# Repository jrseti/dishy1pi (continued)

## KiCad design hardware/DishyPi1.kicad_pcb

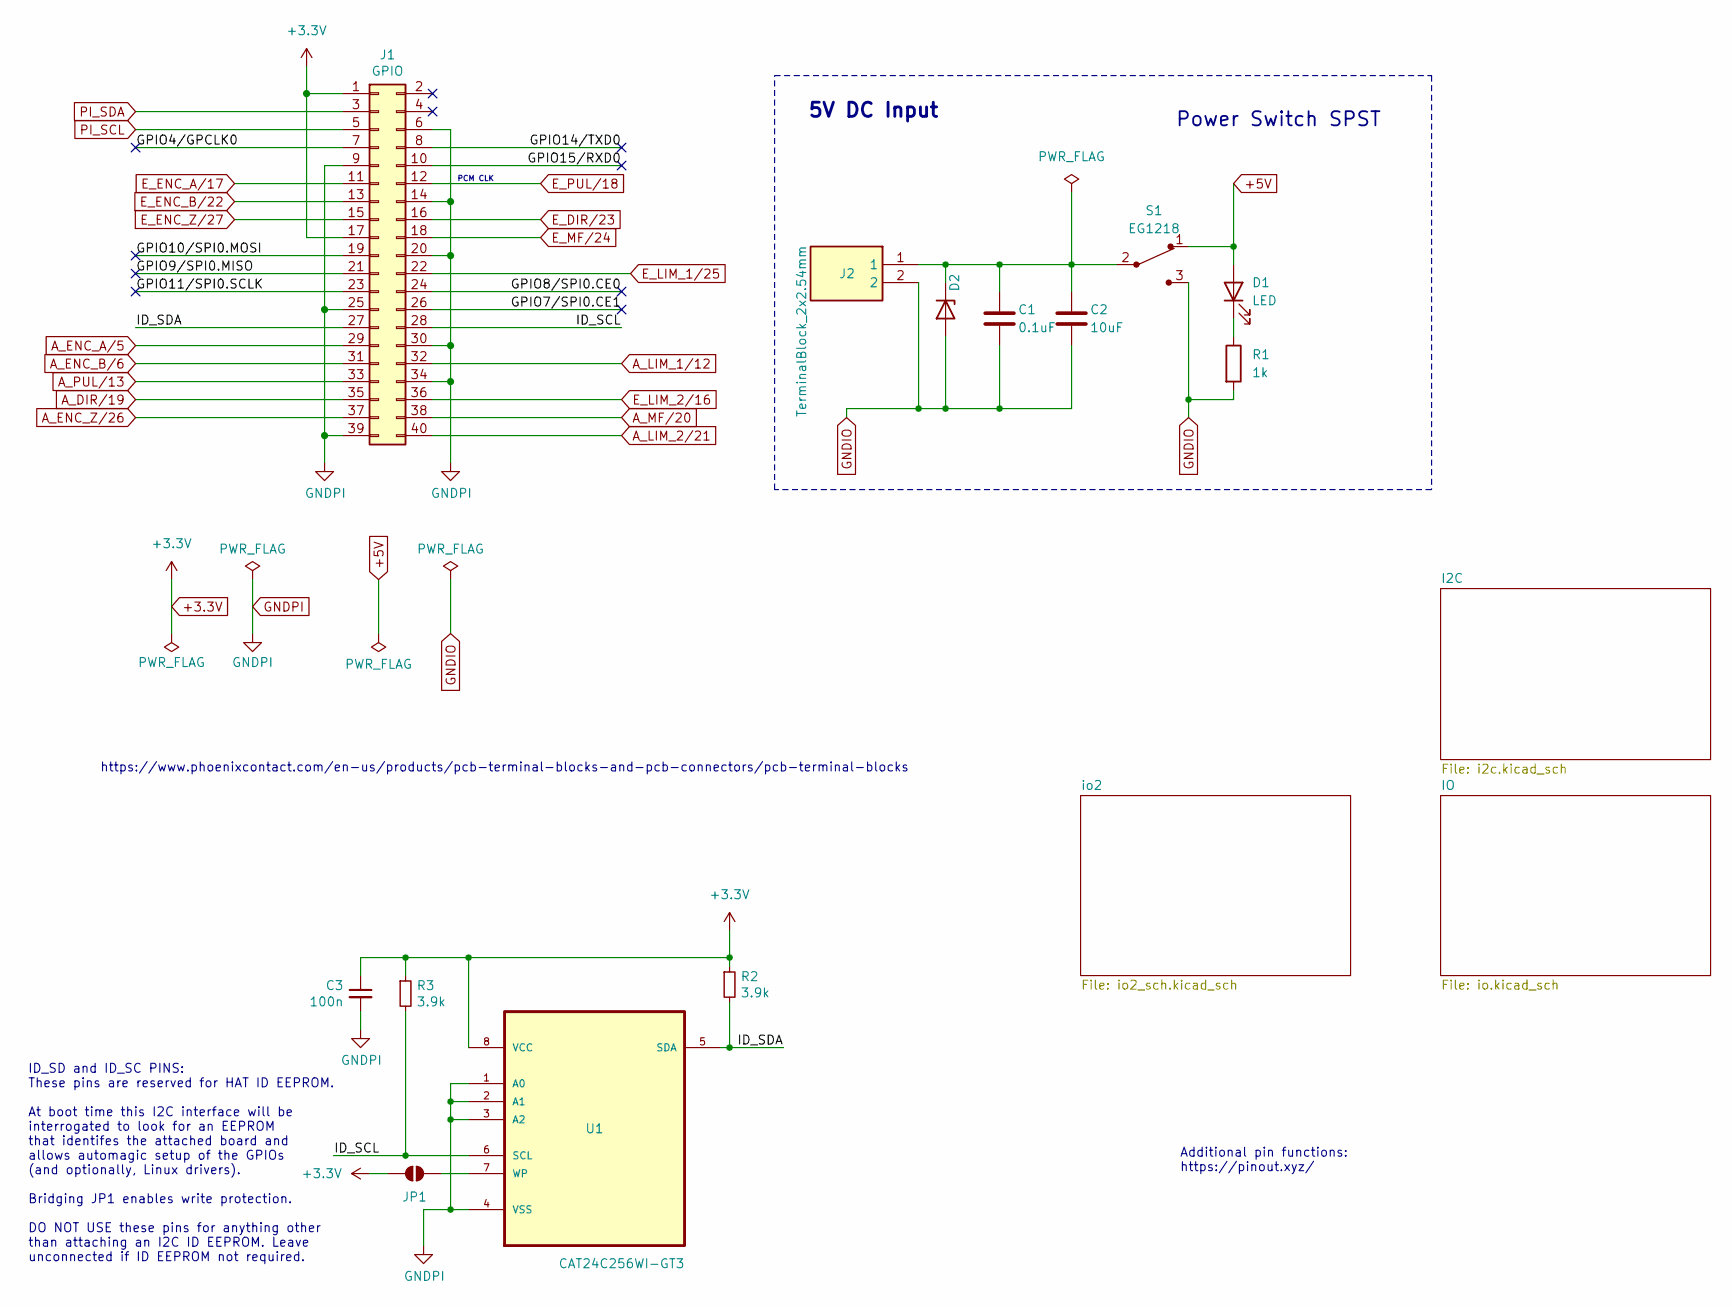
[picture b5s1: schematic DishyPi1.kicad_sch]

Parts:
C1: 0.1uF; C_0402_1005Metric
C2: 10uF; C_0402_1005Metric
C3: 100n; C_0402_1005Metric
D1: LED; LED_1206_3216Metric; LCSC Part C5264252
D2: TPESD0402G05V; D_0402_1005Metric; LCSC C558615
J1: GPIO; PinSocket_2x20_P2.54mm_Vertical
J2: TerminalBlock_2x2.54mm; Manufacturer_Part_Number 1725656; Mouser Part Number 651-1725656
JP1: JP1; Header 1x2 Male
R1: 1k; R_0402_1005Metric; LCSC Part C4410
R2, R3: 3.9k; R_0402_1005Metric
S1: EG1218; Switch_Slide_11.6x4mm_EG1218; MPN EG1218; Digi-Key_PN EG1903-ND
U1: CAT24C256WI-GT3; CAT24C256_EEPROM; MPN CAT24C256WI-GT3

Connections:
+3.3V: C3.1, J1.1, J1.17, JP1.1 (A), R2.1, R3.1, U1.8 (VCC); also elsewhere on the board
+5V: D1.2 (A), S1.1; also elsewhere on the board
/GPIO4/GPCLK0: J1.7
/GPIO7/SPI0.CE1: J1.26
/GPIO8/SPI0.CE0: J1.24
/GPIO9/SPI0.MISO: J1.21
/GPIO10/SPI0.MOSI: J1.19
/GPIO11/SPI0.SCLK: J1.23
/GPIO14/TXD0: J1.8
/GPIO15/RXD0: J1.10
/ID_SCL: J1.28, R3.2, U1.6 (SCL)
/ID_SDA: J1.27, R2.2, U1.5 (SDA)
A_DIR/19: J1.35; also elsewhere on the board
A_ENC_A/5: J1.29; also elsewhere on the board
A_ENC_B/6: J1.31; also elsewhere on the board
A_ENC_Z/26: J1.37; also elsewhere on the board
A_LIM_1/12: J1.32; also elsewhere on the board
A_LIM_2/21: J1.40; also elsewhere on the board
A_MF/20: J1.38; also elsewhere on the board
A_PUL/13: J1.33; also elsewhere on the board
E_DIR/23: J1.16; also elsewhere on the board
E_ENC_A/17: J1.11; also elsewhere on the board
E_ENC_B/22: J1.13; also elsewhere on the board
E_ENC_Z/27: J1.15; also elsewhere on the board
E_LIM_1/25: J1.22; also elsewhere on the board
E_LIM_2/16: J1.36; also elsewhere on the board
E_MF/24: J1.18; also elsewhere on the board
E_PUL/18: J1.12; also elsewhere on the board
GNDIO: C1.2, C2.2, D2.2 (A), J2.2, R1.2, S1.3; also elsewhere on the board
GNDPI: C3.2, J1.6, J1.9, J1.14, J1.20, J1.25, J1.30, J1.34, J1.39, U1.1 (A0), U1.2 (A1), U1.3 (A2), U1.4 (VSS); also elsewhere on the board
unnamed: D1.1 (K), R1.1
unnamed: C1.1, C2.1, D2.1 (K), J2.1, S1.2
unnamed: JP1.2 (B), U1.7 (WP)
PI_SCL: J1.5; also elsewhere on the board
PI_SDA: J1.3; also elsewhere on the board

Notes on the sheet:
PCM CLK
Additional pin functions: https://pinout.xyz/
Power Switch SPST
ID_SD and ID_SC PINS: These pins are reserved for HAT ID EEPROM. At boot time this I2C interface will be interrogated to look for an EEPROM that identifes the attached board and allows automagic setup of the GPIOs (and optionally, Linux drivers). Bridging JP1 enables write protection. DO NOT USE th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
https://www.phoenixcontact.com/en-us/products/pcb-terminal-blocks-and-pcb-connectors/pcb-terminal-blocks
5V DC Input

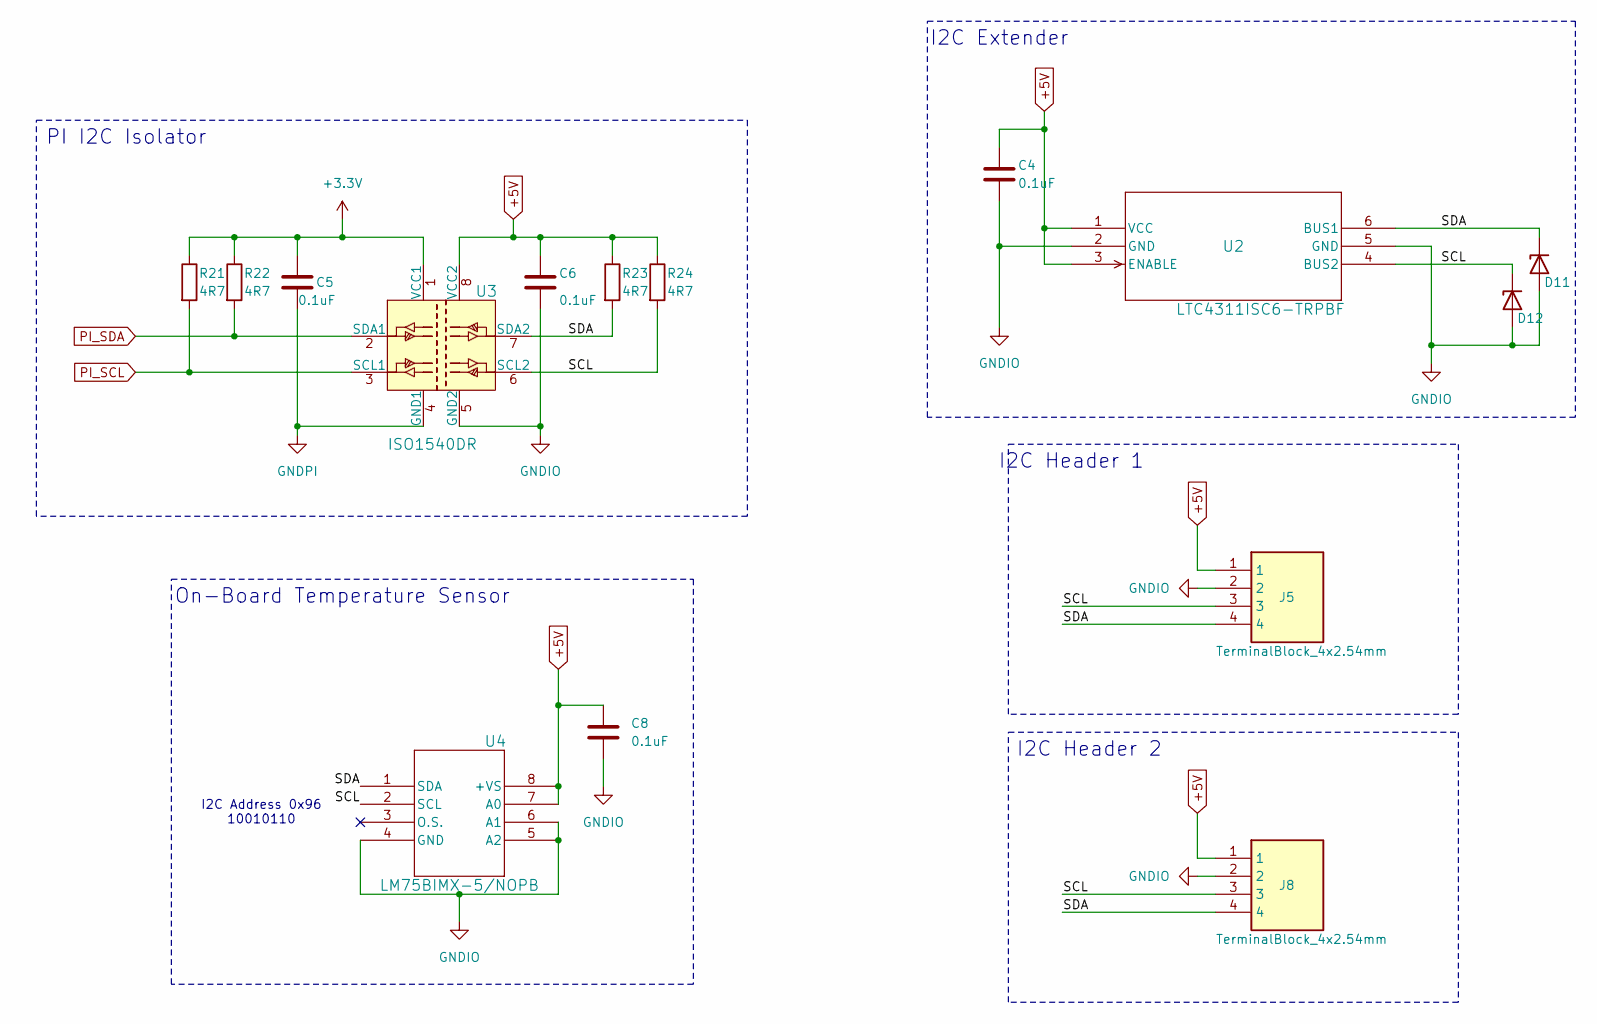
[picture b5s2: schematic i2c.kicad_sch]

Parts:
C4, C5, C6, C8: 0.1uF; C_0402_1005Metric
D11, D12: TPESD0402G05V; D_0402_1005Metric; LCSC C558615
J5, J8: TerminalBlock_4x2.54mm; Manufacturer_Part_Number 1725672; Mouser Part Number 651-1725672
R21, R22, R23, R24: 4R7; R_0402_1005Metric
U2: LTC4311ISC6-TRPBF; LTC4311
U3: ISO1540DR; SOIC-8_W3.9mm; MPN ISO1540DR; Digi-Key_PN 296-34871-1-ND
U4: LM75BIMX-5/NOPB; M08A

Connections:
+3.3V: C5.1, R21.1, R22.1, U3.1 (VCC1); also elsewhere on the board
+5V: C4.1, C6.1, C8.2, J5.1, J8.1, R23.1, R24.1, U2.1 (VCC), U2.3 (ENABLE), U3.8 (VCC2), U4.7 (A0), U4.8 (+VS); also elsewhere on the board
/I2C/SCL: D12.1 (K), J5.3, J8.3, R24.2, U2.4 (BUS2), U3.6 (SCL2), U4.2 (SCL)
/I2C/SDA: D11.1 (K), J5.4, J8.4, R23.2, U2.6 (BUS1), U3.7 (SDA2), U4.1 (SDA)
GNDIO: C4.2, C6.2, C8.1, D11.2 (A), D12.2 (A), J5.2, J8.2, U2.2 (GND), U2.5 (GND), U3.5 (GND2), U4.4 (GND), U4.5 (A2), U4.6 (A1); also elsewhere on the board
GNDPI: C5.2, U3.4 (GND1); also elsewhere on the board
PI_SCL: R21.2, U3.3 (SCL1); also elsewhere on the board
PI_SDA: R22.2, U3.2 (SDA1); also elsewhere on the board

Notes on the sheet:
I2C Header 1
I2C Header 2
PI I2C Isolator
I2C Extender
On-Board Temperature Sensor
I2C Address 0x96 10010110

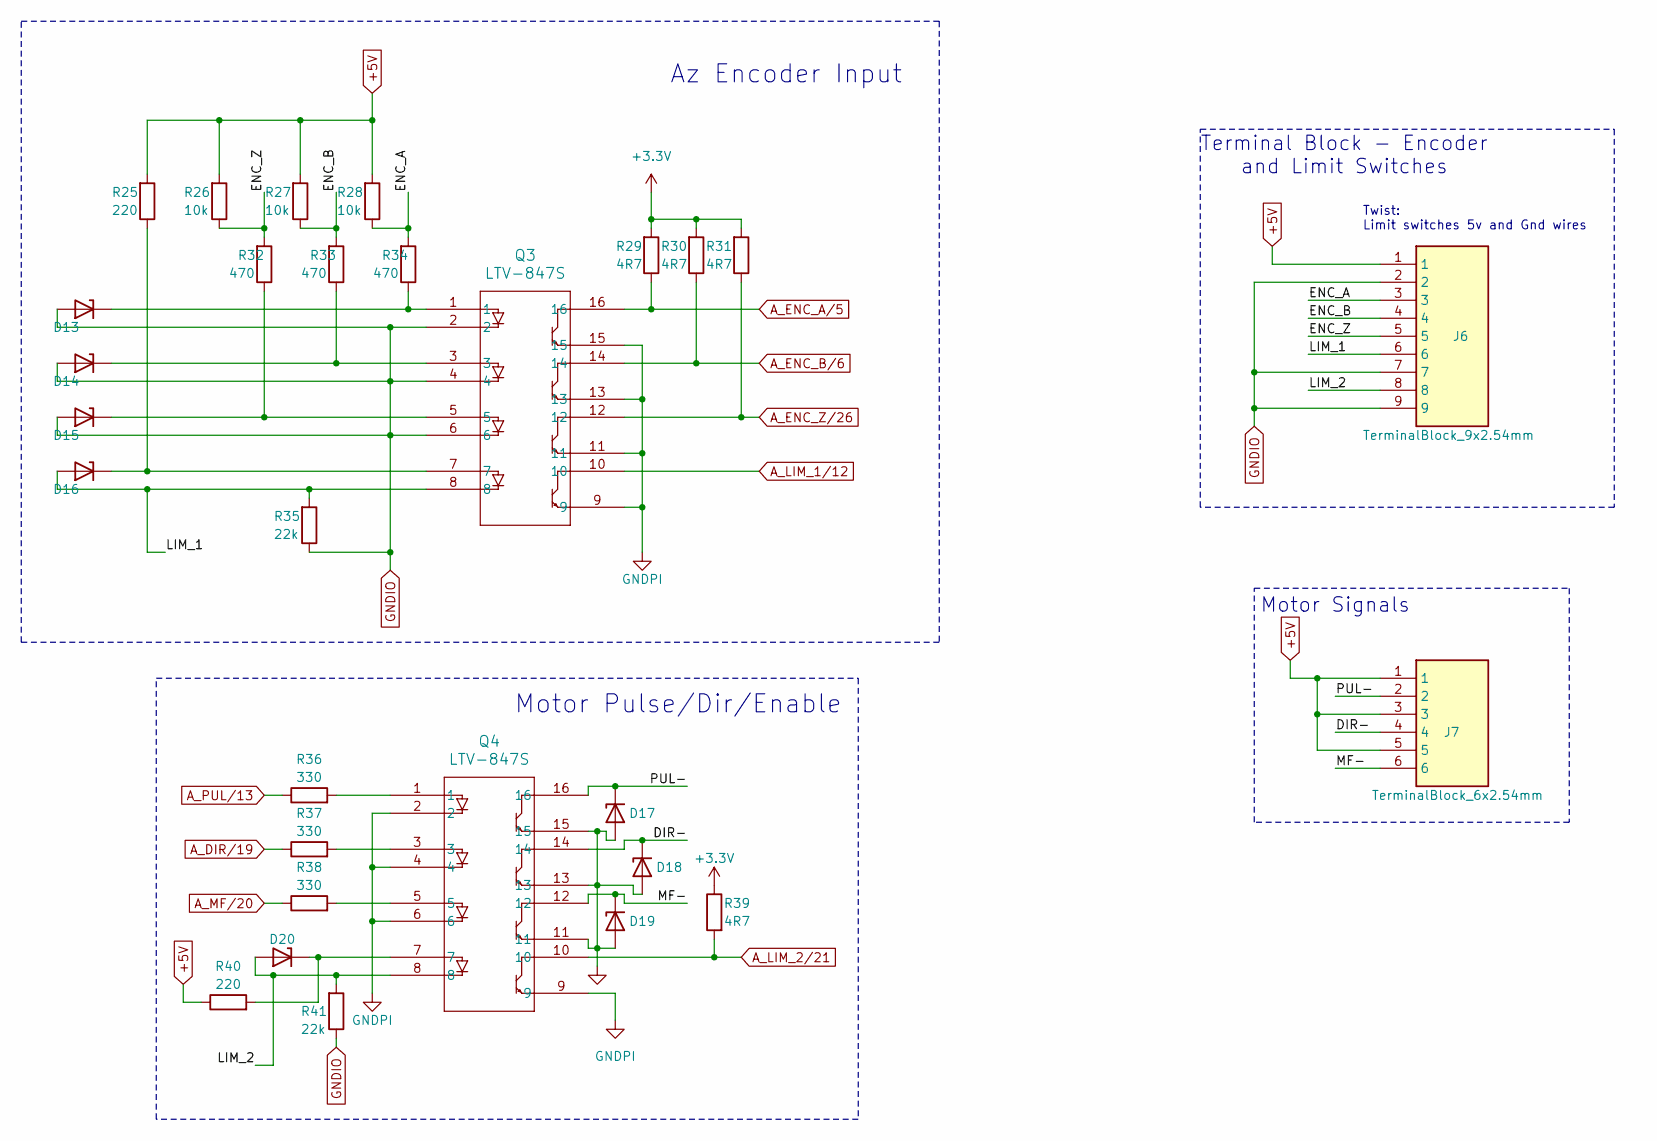
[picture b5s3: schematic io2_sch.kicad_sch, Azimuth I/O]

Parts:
D13, D14, D15, D16, D17, D18, D19, D20: TPESD0402G05V; D_0402_1005Metric; LCSC C558615
J6: TerminalBlock_9x2.54mm; Manufacturer_Part_Number 1725724; Mouser Part Number 651-1725724
J7: TerminalBlock_6x2.54mm; Manufacturer_Part_Number 1725698; Mouser Part Number 651-1725698
Q3, Q4: LTV-847S; ACPL-847-300E
R25, R40: 220; R_0402_1005Metric
R26, R27, R28: 10k; R_0402_1005Metric
R29, R30, R31, R39: 4R7; R_0402_1005Metric
R32, R33, R34: 470; R_0402_1005Metric
R35: 22k; R_0201_0603Metric
R36, R37, R38: 330; R_0402_1005Metric
R41: 22k; R_0402_1005Metric

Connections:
+3.3V: R29.2, R30.2, R31.2, R39.1; also elsewhere on the board
+5V: J6.1, J7.1, J7.3, J7.5, R25.2, R26.2, R27.2, R28.2, R40.1; also elsewhere on the board
/io2/DIR-: D18.1 (K), J7.4, Q4.14
/io2/ENC_A: J6.3, R28.1, R34.2
/io2/ENC_B: J6.4, R27.1, R33.2
/io2/ENC_Z: J6.5, R26.1, R32.2
/io2/LIM_1: D16.2 (A), J6.6, Q3.8, R35.2
/io2/LIM_2: D20.2 (A), J6.8, Q4.8, R41.2
/io2/MF-: D19.1 (K), J7.6, Q4.12
/io2/PUL-: D17.1 (K), J7.2, Q4.16
A_DIR/19: R37.1; also elsewhere on the board
A_ENC_A/5: Q3.16, R29.1; also elsewhere on the board
A_ENC_B/6: Q3.14, R30.1; also elsewhere on the board
A_ENC_Z/26: Q3.12, R31.1; also elsewhere on the board
A_LIM_1/12: Q3.10; also elsewhere on the board
A_LIM_2/21: Q4.10, R39.2; also elsewhere on the board
A_MF/20: R38.1; also elsewhere on the board
A_PUL/13: R36.1; also elsewhere on the board
GNDIO: D13.2 (A), D14.2 (A), D15.2 (A), D17.2 (A), D18.2 (A), D19.2 (A), J6.2, J6.7, J6.9, Q3.2, Q3.4, Q3.6, Q4.11, Q4.13, Q4.15, R35.1, R41.1; also elsewhere on the board
GNDPI: Q3.9, Q3.11, Q3.13, Q3.15, Q4.2, Q4.4, Q4.6, Q4.9; also elsewhere on the board
unnamed: D13.1 (K), Q3.1, R34.1
unnamed: D14.1 (K), Q3.3, R33.1
unnamed: D15.1 (K), Q3.5, R32.1
unnamed: D16.1 (K), Q3.7, R25.1
unnamed: D20.1 (K), Q4.7, R40.2
unnamed: Q4.1, R36.2
unnamed: Q4.3, R37.2
unnamed: Q4.5, R38.2

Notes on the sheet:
Az Encoder Input
Twist: Limit switches 5v and Gnd wires
Motor Signals
Terminal Block - Encoder and Limit Switches
Motor Pulse/Dir/Enable

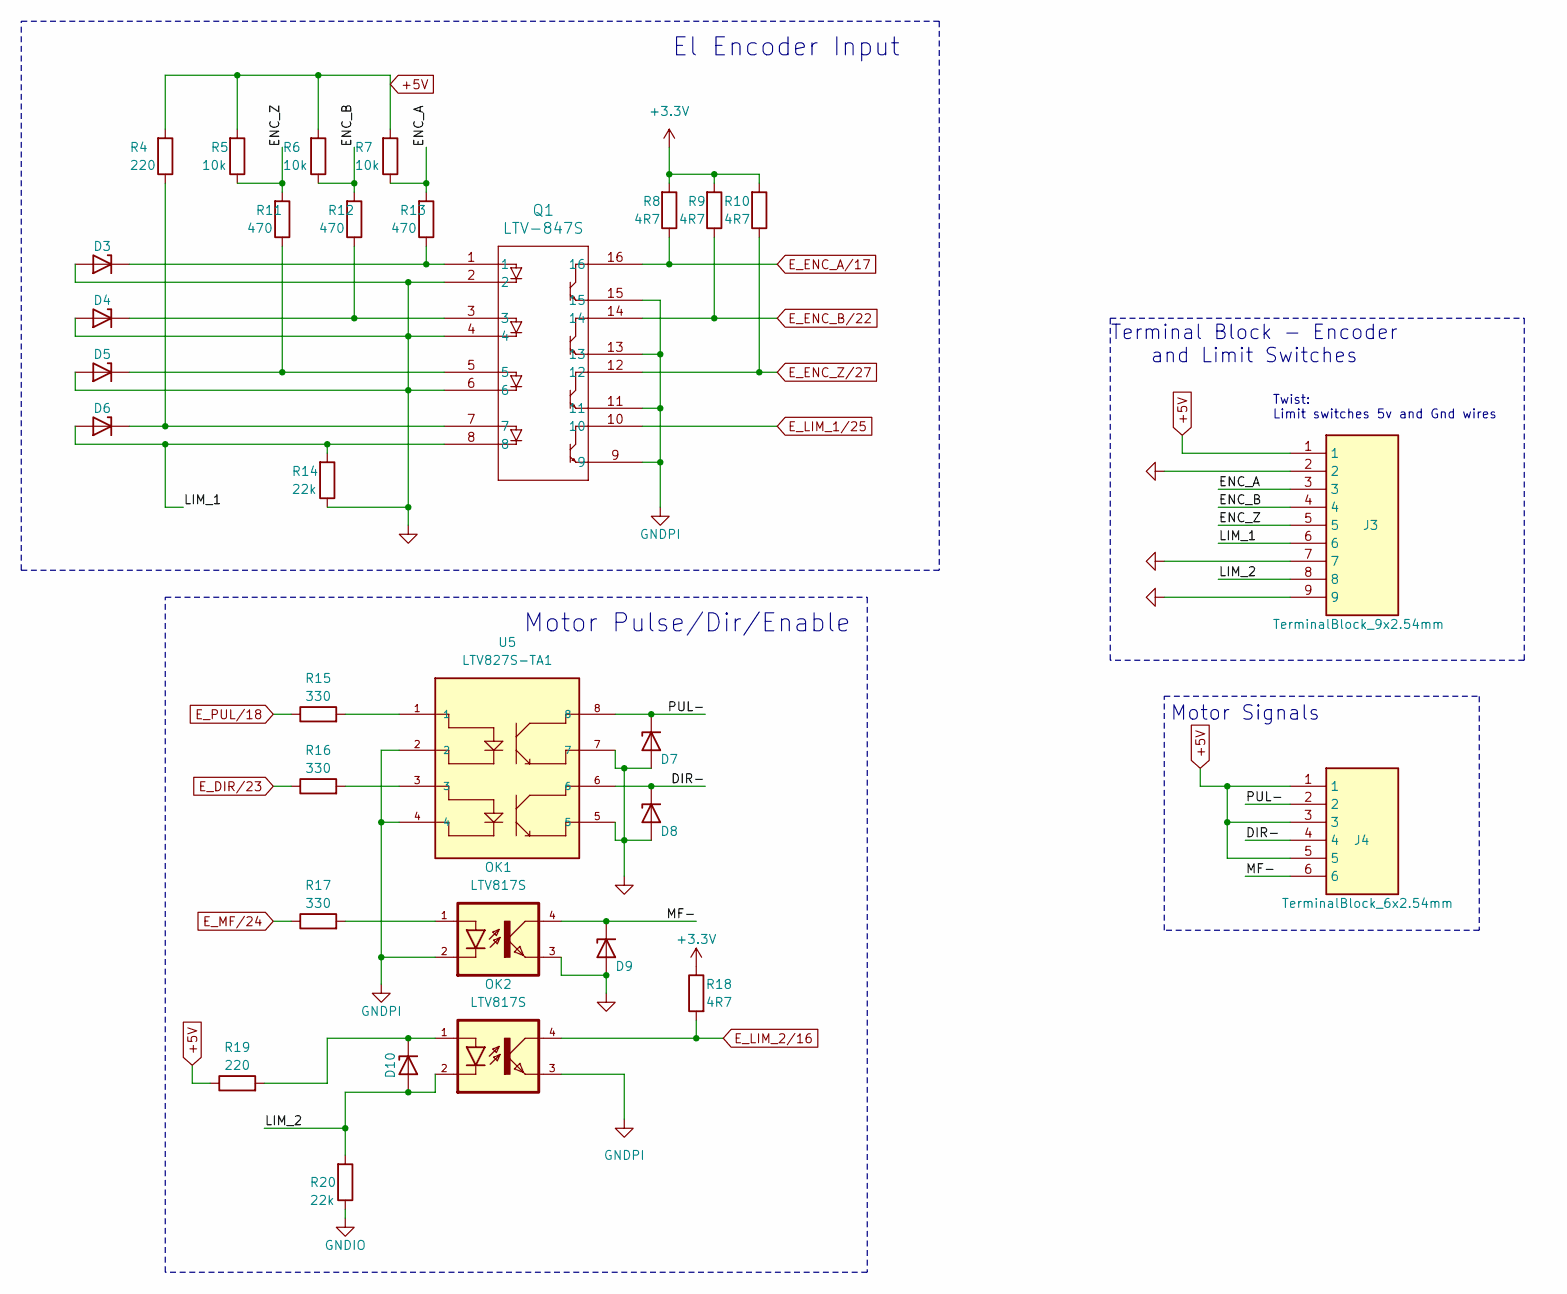
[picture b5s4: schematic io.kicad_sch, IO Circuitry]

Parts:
D3, D4, D5, D6, D7, D8, D9, D10: TPESD0402G05V; D_0402_1005Metric; LCSC C558615
J3: TerminalBlock_9x2.54mm; Manufacturer_Part_Number 1725724; Mouser Part Number 651-1725724
J4: TerminalBlock_6x2.54mm; Manufacturer_Part_Number 1725698; Mouser Part Number 651-1725698
OK1, OK2: LTV817S; MPN LTV-817S; LCSC C125121
Q1: LTV-847S; LTV847S
R4, R19: 220; R_0402_1005Metric
R5, R6, R7: 10k; R_0402_1005Metric
R8, R9, R10, R18: 4R7; R_0402_1005Metric
R11, R12, R13: 470; R_0402_1005Metric
R14, R20: 22k; R_0402_1005Metric
R15, R16, R17: 330; R_0402_1005Metric
U5: LTV827S-TA1; LTV827S; PARTNO 160-2040-1-ND; DigiKey_Part_Number 160-2040-1-ND

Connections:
+3.3V: R8.2, R9.2, R10.2, R18.1; also elsewhere on the board
+5V: J3.1, J4.1, J4.3, J4.5, R4.2, R5.2, R6.2, R7.2, R19.1; also elsewhere on the board
/IO/DIR-: D8.1 (K), J4.4, U5.6
/IO/ENC_A: J3.3, R7.1, R13.2
/IO/ENC_B: J3.4, R6.1, R12.2
/IO/ENC_Z: J3.5, R5.1, R11.2
/IO/LIM_1: D6.2 (A), J3.6, Q1.8, R14.2
/IO/LIM_2: D10.2 (A), J3.8, OK2.2, R20.2
/IO/MF-: D9.1 (K), J4.6, OK1.4
/IO/PUL-: D7.1 (K), J4.2, U5.8
E_DIR/23: R16.1; also elsewhere on the board
E_ENC_A/17: Q1.16, R8.1; also elsewhere on the board
E_ENC_B/22: Q1.14, R9.1; also elsewhere on the board
E_ENC_Z/27: Q1.12, R10.1; also elsewhere on the board
E_LIM_1/25: Q1.10; also elsewhere on the board
E_LIM_2/16: OK2.4, R18.2; also elsewhere on the board
E_MF/24: R17.1; also elsewhere on the board
E_PUL/18: R15.1; also elsewhere on the board
GNDIO: D3.2 (A), D4.2 (A), D5.2 (A), D7.2 (A), D8.2 (A), D9.2 (A), J3.2, J3.7, J3.9, OK1.3, Q1.2, Q1.4, Q1.6, R14.1, R20.1, U5.5, U5.7; also elsewhere on the board
GNDPI: OK1.2, OK2.3, Q1.9, Q1.11, Q1.13, Q1.15, U5.2, U5.4; also elsewhere on the board
unnamed: D3.1 (K), Q1.1, R13.1
unnamed: D4.1 (K), Q1.3, R12.1
unnamed: D5.1 (K), Q1.5, R11.1
unnamed: D6.1 (K), Q1.7, R4.1
unnamed: D10.1 (K), OK2.1, R19.2
unnamed: OK1.1, R17.2
unnamed: R15.2, U5.1
unnamed: R16.2, U5.3

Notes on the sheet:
Terminal Block - Encoder and Limit Switches
Twist: Limit switches 5v and Gnd wires
Motor Signals
El Encoder Input
Motor Pulse/Dir/Enable

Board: 4 copper layers, 92 parts (1 on the bottom side), 61 nets, no tracks yet.

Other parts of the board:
MH1, MH2, MH3, MH4: MountingHole_2.7mm_M2.5

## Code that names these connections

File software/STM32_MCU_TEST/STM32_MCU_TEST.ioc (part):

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Mcu.Name=STM32G474C(B-C-E)Tx
Mcu.Package=LQFP48
Mcu.UserName=STM32G474CETx
PA0.GPIOParameters=GPIO_Label
PA0.GPIO_Label=ENC1_A
PA0.Signal=S_TIM2_CH1
PA1.GPIOParameters=GPIO_Label
PA1.GPIO_Label=ENC1_B
PA1.Signal=S_TIM2_CH2
PA13.Mode=Serial_Wire
PA13.Signal=SYS_JTMS-SWDIO
PA14.Mode=Serial_Wire
PA14.Signal=SYS_JTCK-SWCLK
PA2.GPIOParameters=GPIO_Label,GPIO_ModeDefaultEXTI
PA2.GPIO_Label=ENC1_Z
PA2.GPIO_ModeDefaultEXTI=GPIO_MODE_IT_FALLING
PA2.Signal=GPXTI2
PA4.GPIOParameters=GPIO_Label
PA4.GPIO_Label=LIMIT1_SW1
PA4.Signal=GPIO_Input
PA5.GPIOParameters=GPIO_Label
PA5.GPIO_Label=LIMIT1_SW2
PA5.Signal=GPIO_Input
PA6.GPIOParameters=GPIO_Label
PA6.GPIO_Label=ENABLE1
PA6.Signal=GPIO_Output
PA7.GPIOParameters=GPIO_Label
PA7.GPIO_Label=DIR1
PA7.Signal=GPIO_Output
PA8.GPIOParameters=GPIO_Label
PA8.GPIO_Label=I2C_SCL
PA8.Mode=I2C
PA8.Signal=I2C3_SCL
PB0.GPIOParameters=GPIO_Label
PB0.GPIO_Label=PUL1
PB0.Signal=S_TIM3_CH3
PB3.Signal=SYS_JTDO-SWO
PB5.GPIOParameters=GPIO_Label
PB5.GPIO_Label=I2C_SDA
PB5.Mode=I2C
PB5.Signal=I2C3_SDA
PB6.GPIOParameters=GPIO_Label
PB6.GPIO_Label=USART1_TX
PB6.Mode=Asynchronous
PB6.Signal=USART1_TX
PB7.GPIOParameters=GPIO_Label,GPIO_PuPd
PB7.GPIO_Label=USART1_RX
PB7.GPIO_PuPd=GPIO_PULLUP
PB7.Mode=Asynchronous
PB7.Signal=USART1_RX
PB8-BOOT0.GPIOParameters=GPIO_Label
PB8-BOOT0.GPIO_Label=Boot0
PB8-BOOT0.Signal=GPIO_Input
PF0-OSC_IN.Mode=HSE-External-Oscillator
PF0-OSC_IN.Signal=RCC_OSC_IN
PF1-OSC_OUT.Mode=HSE-External-Oscillator
PF1-OSC_OUT.Signal=RCC_OSC_OUT
RCC.HSE_VALUE=16000000
RCC.SYSCLKFreq_VALUE=170000000
RCC.SYSCLKSource=RCC_SYSCLKSOURCE_PLLCLK
board=custom

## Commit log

2025-09-20 Added python ignores
2025-09-20 Added hardware KiCad project
2025-09-20 Added requirements.txt with easyeda2kicad installed
2025-09-20 Added content
2025-09-20 Added the LTV parts, and an image for the README
2025-09-21 Removed ignoring kicad_prl
2025-09-21 Added README and parts.txt
2025-09-21 Moved kicad files into new dishy1pi dir
2025-09-21 Moves kicad files into dishy1pi dir
2025-09-21 Added new version adter dir changes
2025-09-21 Added power_supply
2025-09-21 Fleshed out the BOM
2025-09-21 Updated BOM
2025-09-21 Added parts.bat, imporoved README
2025-09-28 Parts place in PCB layout
2025-09-30 Ground and Power planes placed
2025-11-23 Added parts libs
2025-11-23 Modifications based on first board assembly
2025-11-23 Added logo images
2025-11-23 Added jlcpcb dir
2025-11-23 Firs PCB and scheamtic push
2025-11-23 Added pwr_12v_in.kicad_sch
2025-11-23 Added power circuit to dishy schematic
2025-11-23 New PCB layout started
2025-12-06 Added 12V power input
2025-12-06 Little change
2025-12-25 First commit of mcu_test_board
2025-12-25 Pushed latest parts lib
2025-12-25 STM32 code first commit
2025-12-25 Schematic minor improvements - one axis so far
2025-12-31 Some code written
2025-12-31 Added STM32G431KBT6TR to lib
2026-03-18 Latest mcu_test_board
2026-03-22 Parts cleaned up, board ordered
2026-03-23 Added STM32_MCU_TEST_32PIN
2026-03-23 Added .mxproject, adjusted .gitignore
2026-03-23 Removed .mxproject
2026-03-28 32 pin MCU software
2026-03-28 Adjusting parts
2026-03-28 MCU files
